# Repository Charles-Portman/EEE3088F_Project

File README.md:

# EEE3088F_Project
 
The project will be a Self-Contained Light Sensing Module.
This will include an ambient light digital sensor and an analog voltage divider using photoresistors (Amount dependant on budget).
The module will include EEEPROM and battery power.
The prupose of the Git is for the programming of the microcontroller to FTDI-USB converter, EEPROM read and write, Reading from the sensors using I2C and the on-board ADC of the microcintroller.

NOTE - Additionally a low power standby mode may be added

Proposed branches 
- Sensors
 - ADC sensing
 - Digital Sensing
- Storage
- External Communication

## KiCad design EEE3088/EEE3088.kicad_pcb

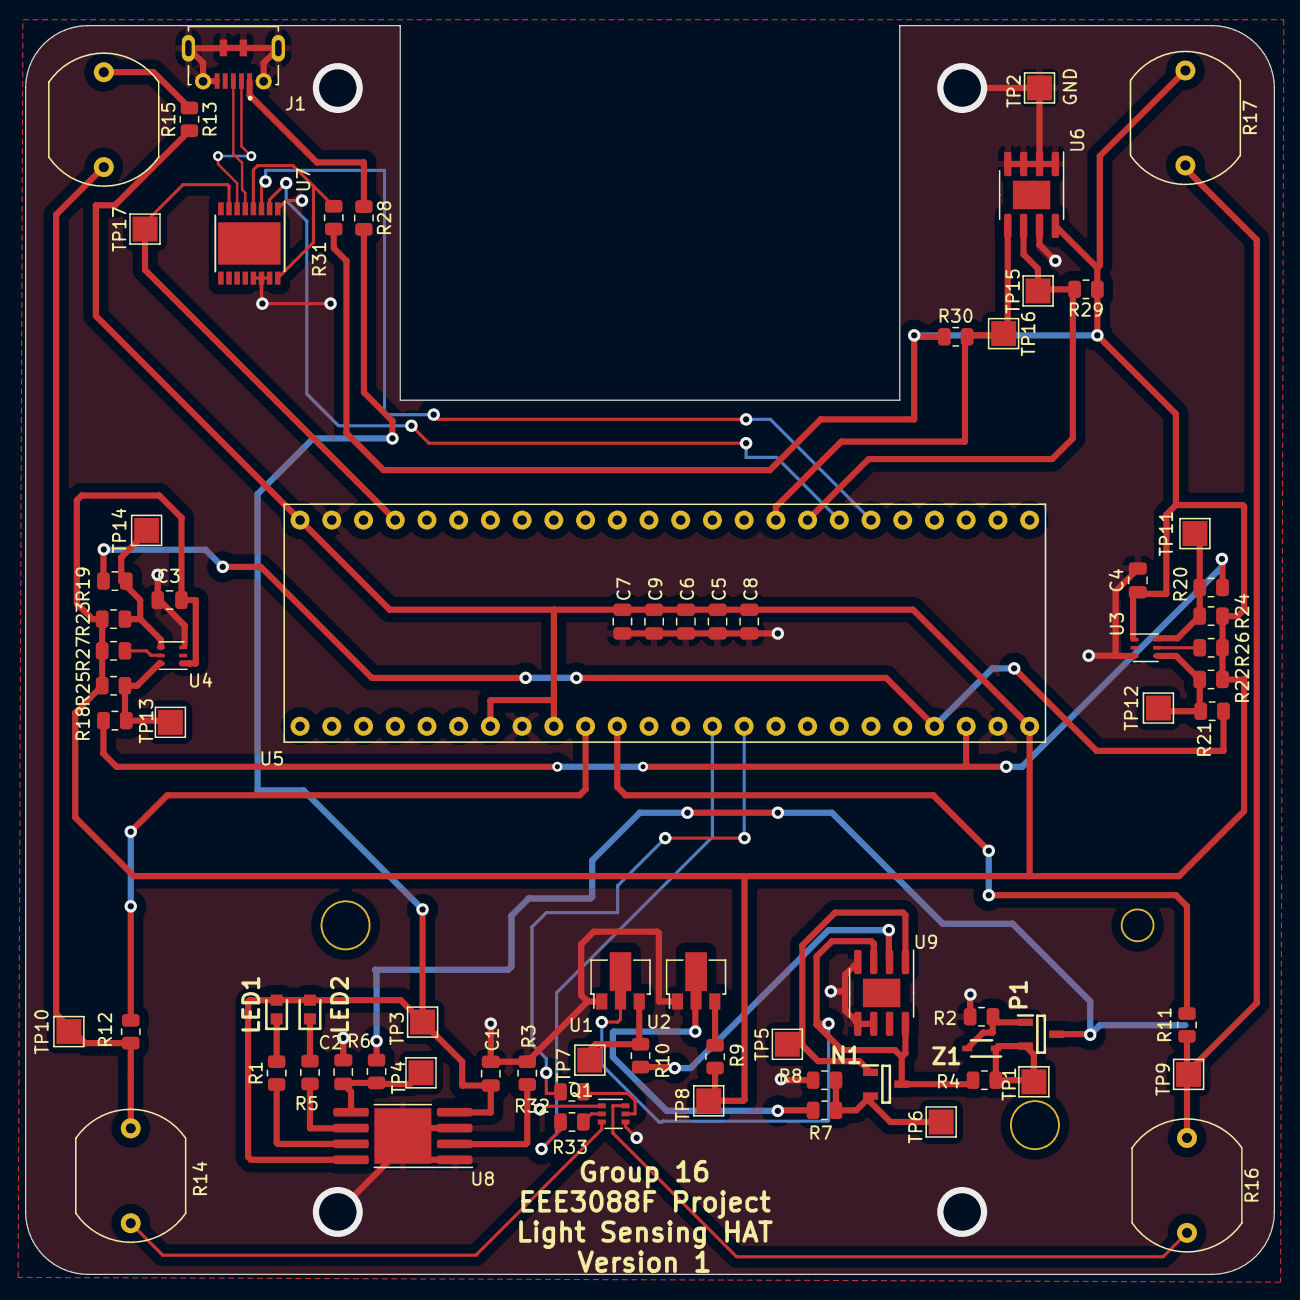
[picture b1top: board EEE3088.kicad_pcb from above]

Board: 2 copper layers, 100.0 x 100.0 mm, 76 parts (1 on the bottom side), 47 nets.

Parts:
Battery-Holder1: BH-18650-PC; 18650_Holder_SMD
C1, C2: 10uF; C_0805_2012Metric
C3, C4, C9: 1uF; C_0805_2012Metric
C5, C6: 100nF; C_0805_2012Metric
C7: 4.7uF; C_0805_2012Metric
C8: 10nF; C_0805_2012Metric
J1: MICROXNJ; SHOUHAN_MICROXNJ
LED1: Red; LEDC1608X70N
LED2: Green; LEDC1608X50N
N1: AO3400A; SOT95P280X125-3N
P1: AO3401A; SOT95P280X125-3N
Q1: MMDT2222A; SOT-363_SC-70-6
R1, R5: 1k; R_0805_2012Metric
R2: 100k; R_0805_2012Metric
R3: 1.2k; R_0805_2012Metric
R4, R6, R7, R9, R10, R11, R12, R13, R18, R19, R20, R21, R28, R31: 0; R_0805_2012Metric
R8: 1M; R_0805_2012Metric
R14, R15, R16, R17: LDR03; R_LDR_10x8.5mm_P7.6mm_Vertical
R22, R23, R24, R25, R26, R27: 10K; R_0805_2012Metric
R29, R30: 1.8k; R_0805_2012Metric
R32, R33: 1K; R_0805_2012Metric
TP1, TP2, TP3, TP4, TP5, TP6, TP7, TP8, TP9, TP10, TP11, TP12, TP13, TP14, TP15, TP16, TP17: TestPoint; TestPoint_Pad_2.0x2.0mm
U1, U2: HT7533-1; SOT-89-3
U3, U4: LTR-303ALS-01; Lite-On_LTR-303ALS-01
U5: Header; STM32F051C6T6
U6: AT24C256C-SSHL-T; SOIC-8-1EP_3.9x4.9mm_P1.27mm_EP2.29x3mm
U7: CH340G; HTSSOP-16-1EP_4.4x5mm_P0.65mm_EP3.4x5mm
U8: TP4056; SOP-8-1EP_4.57x4.57mm_P1.27mm_EP4.57x4.45mm
U9: MCP6002T-I_SN; SOIC-8-1EP_3.9x4.9mm_P1.27mm_EP2.29x3mm
Z1: MM3Z5V6C; SODFL2513X100N

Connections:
+3.3V: C3.1, C4.1, C5.1, C6.1, C7.1, C8.1, C9.1, R9.2, R13.2, R17.1, R22.1, R23.1, R24.1, R25.1, R26.1, R27.1, R29.1, R30.1, R31.1, TP8.1, U3.1 (VDD), U4.1 (VDD), U5.7 (NRST), U5.9 (V+), U5.24 (V+), U5.48 (V+), U6.8 (VCC)
+5V: C1.1, LED1.2, LED2.2, R28.2, TP3.1, U8.4 (VCC), U8.8 (CE)
/Microcontroller/Analogue_Enable1: R33.1, U5.14 (PA4)
/Microcontroller/Analogue_Enable2: R32.1, U5.15 (PA5)
/Microcontroller/EEPROM_SCL: R29.2, TP15.1, U5.32 (PA11), U6.6 (SCL)
/Microcontroller/EEPROM_SDA: R30.2, TP16.1, U5.33 (PA12), U6.5 (SDA)
/Microcontroller/LDR_Vout1: R11.2, U5.11 (PA1)
/Microcontroller/LDR_Vout2: R12.1, U5.10 (PA0)
/Microcontroller/SCLSense: R19.1, R21.1, U5.21 (PB10)
/Microcontroller/SDASense_1: R18.1, R20.2, U5.22 (PB11)
/Microcontroller/USB_D+: J1.3 (D+), U7.5 (UD+)
/Microcontroller/USB_D-: J1.2 (D-), U7.6 (UD-)
/Microcontroller/USB_RXD: U5.30 (PA9), U7.3 (RXD)
/Microcontroller/USB_TIMIN: TP17.1, U5.45 (PB8), U7.7 (XI)
/Microcontroller/USB_TXD: U5.31 (PA10), U7.2 (TXD)
/Power_Subsystem/3.3-back: R10.2, U9.2 (VINA-)
/Power_Subsystem/V-Reg: R7.2, U2.2 (VI)
/Power_Subsystem/V-pos: N1.3, R4.2, U1.2 (VI), U9.3 (VINA+), U9.8 (VDD)
/Power_Subsystem/Vbat: Battery-Holder1.1, P1.3, R6.2
GND: Battery-Holder1.2, C1.2, C2.2, C3.2, C4.2, C5.2, C6.2, C7.2, C8.2, C9.2, J1.5 (GND), J1.S1 (SHIELD), J1.S2 (SHIELD), J1.S3 (SHIELD), J1.S4 (SHIELD), J1.S5 (SHIELD), J1.S6 (SHIELD), Q1.1 (E1), Q1.4 (E2), R2.1, R3.1, R8.2, TP2.1, U1.1, U2.1, U3.3 (GND), U4.3 (GND), U5.8 (GND), U5.23 (GND), U5.47 (GND), U6.1 (A0), U6.2 (A1), U6.3 (A2), U6.4 (GND), U6.7 (WP), U7.1 (GND), U7.13 (~DTR), U7.14 (~RTS), U7.15 (RS232), U8.1 (TEMP), U8.3 (GND), U8.9 (EP), U9.4 (VSS), U9.5 (VINB+), U9.6 (VINB-)
unnamed: J1.1 (VBUS), R28.1
unnamed: LED1.1, R1.2
unnamed: LED2.1, R5.1
unnamed: N1.2, R7.1, R8.1, TP6.1
unnamed: Q1.2 (B1), R33.2
unnamed: Q1.6 (C1), R16.2
unnamed: Q1.5 (B2), R32.2
unnamed: Q1.3 (C2), R14.2
unnamed: R11.1, R16.1, R17.2, TP9.1
unnamed: R12.2, R14.1, R15.2, TP10.1
unnamed: R13.1, R15.1
unnamed: R10.1, TP7.1, U1.3 (VO)
unnamed: R9.1, U2.3 (VO)
unnamed: R26.2, U3.5 (INT)
unnamed: R21.2, R22.2, TP12.1, U3.4 (SCL)
unnamed: R20.1, R24.2, TP11.1, U3.6 (SDA)
unnamed: R27.2, U4.5 (INT)
unnamed: R19.2, R23.2, TP14.1, U4.4 (SCL)
unnamed: R18.2, R25.2, TP13.1, U4.6 (SDA)
unnamed: R31.2, U7.4 (V3), U7.16 (VCC)
unnamed: C2.1, R6.1, TP4.1, U8.5 (BAT)
unnamed: R3.2, U8.2 (PROG)
unnamed: R1.1, U8.7 (~CHRG)
unnamed: R5.2, U8.6 (~STDBY)
unnamed: N1.1, TP5.1, U9.1 (VOUTA)
unnamed: P1.1, R2.2, Z1.2 (A)
unnamed: P1.2, R4.1, TP1.1, Z1.1 (K)

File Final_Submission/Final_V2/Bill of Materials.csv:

Comment,Designator,Footprint,JLCPCB Part#
10uF Cap 0805,"C1, C2",0805_C,C15850
1uF Cap 0805,"C3, C4, C9",0805_C,C28323
100nF Cap 0805,"C5, C6",0805_C,C49678
4.7uF Cap 0805,C7,0805_C,C1779
10nF Cap 0805,C8,0805_C,C1710
USB Connector,J1,MICROXNJ,C404969
Red LED,LED1,LEDC1608X70N,C2286
Green LED,LED2,LEDC1608X50N,C72043
30V N-Channel MOSFET,N1,SOT95P280X125-3N,C20917
30V P-Channel MOSFET,P1,SOT95P280X125-3N,C15127
Dual NPN Transistor,Q1,SOT-363_SC-70-6,C96379
1k Resistor 0805,"R1, R5, R32, R33",0805_R,C17513
100k Resistor 0805,R2,0805_R,C149504
1.2k Resistor 0805,R3,0805_R,C17379
0 Resistor 0805,"R4, R6, R7, R9-R13, R18-R21, R28, R31",0805_R,C17477
1M Resistor 0805,R8,0805_R,C17514
LDR,R14-R17,R_LDR_10x8.5mm_P7.6mm_Vertical,C11287
10K Resistor 0805,R22-R27,0805_R,C17414
1.8k Res 0805,"R29, R30",0805_R,C17398
Voltage Regulator,"U1, U2",SOT-89-3,C14289
ALS,"U3, U4",LTR-303ALS-01,C364577
EEPROM,U6,SOIC-8-1EP_3.9x4.9mm_P1.27mm_EP2.29x3mm,C6482
USB Comms ,U7,HTSSOP-16-1EP_4.4x5mm_P0.65mm_EP3.4x5mm,C14267
Battery Charger,U8,SOP-8-1EP_4.57x4.57mm_P1.27mm_EP4.57x4.45mm,C16581
Op-Amp,U9,SOIC-8-1EP_3.9x4.9mm_P1.27mm_EP2.29x3mm,C7377
Zener diode,Z1,SODFL2513X100N,C48886

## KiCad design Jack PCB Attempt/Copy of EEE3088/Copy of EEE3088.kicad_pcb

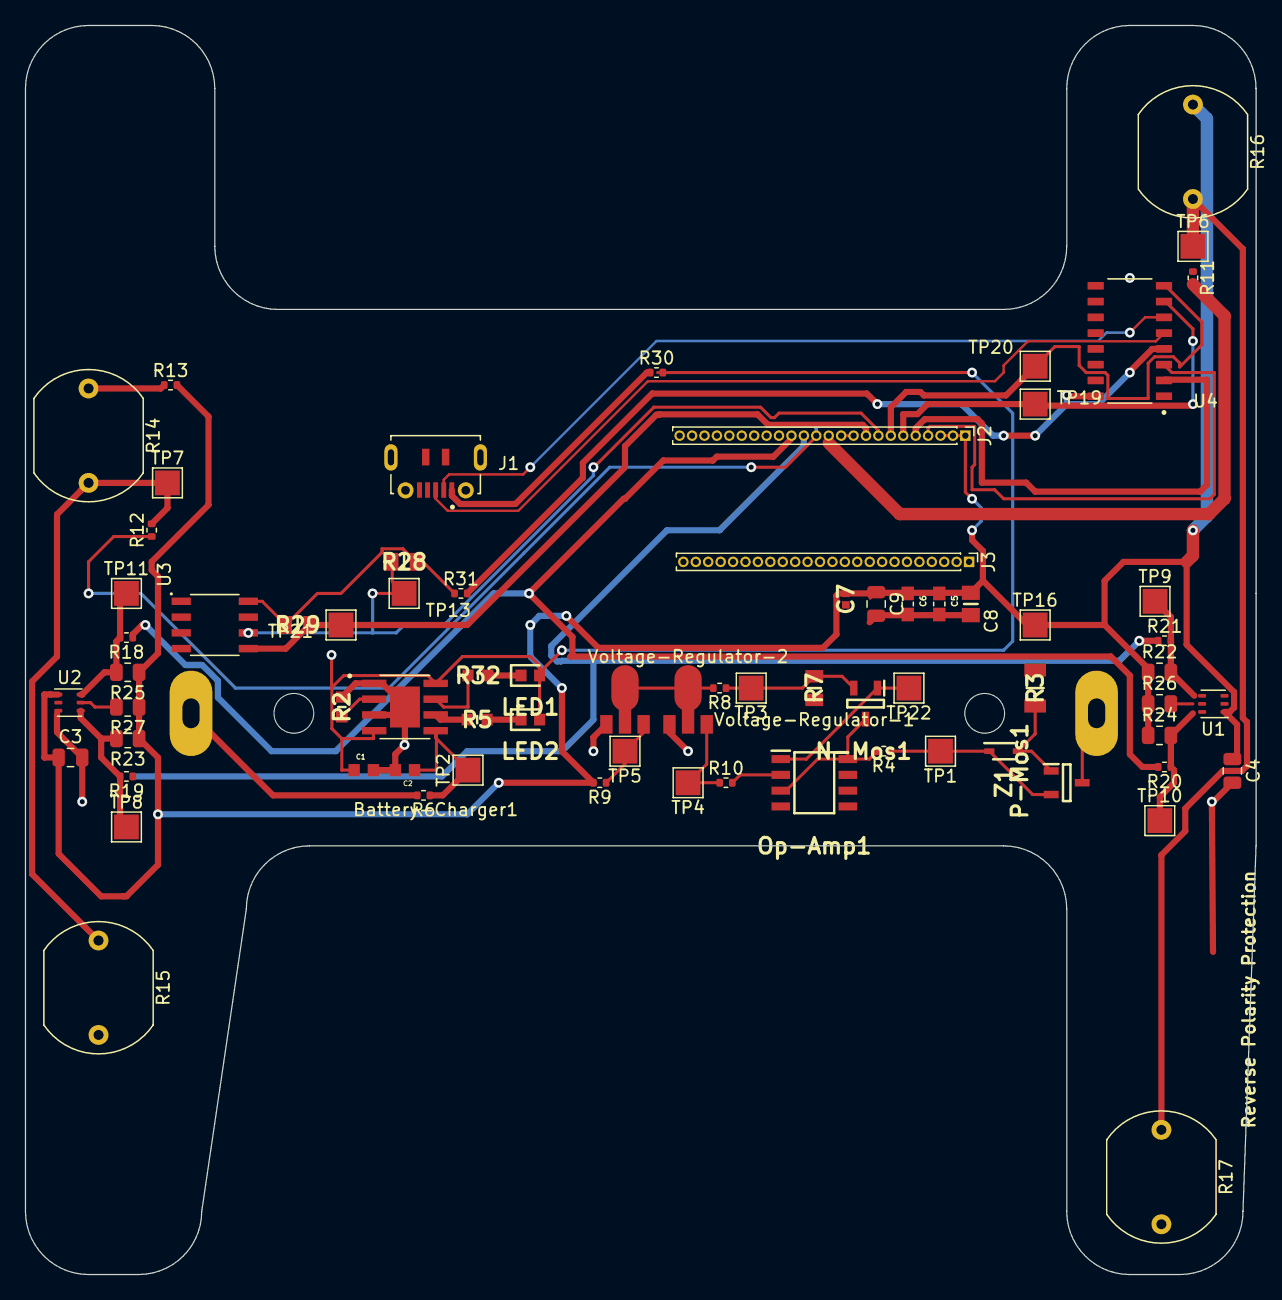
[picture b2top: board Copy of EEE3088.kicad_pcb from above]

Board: 2 copper layers, 99.1 x 100.5 mm, 74 parts (1 on the bottom side), 44 nets.

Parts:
Battery-Charger1: TP4056; SOP127P600X175-9N
Battery-Holder1: BH-18650-PC; BAT_BH-18650-PC
C1, C2: 10uF; CAPC1608X90N
C3, C4, C9: 1uF; C_0805_2012Metric
C5, C6: 100nF; CAPC1608X90
C7: 4.7uF; CAPC1005X55N
C8: 10nF; CAPC2012X140N
J1: MICROXNJ; SHOUHAN_MICROXNJ
J2, J3: Conn_01x24; PinHeader_1x24_P1.00mm_Vertical
LED1: Red; LEDC1608X70N
LED2: Green; LEDC1608X50N
N-Mos1: AO3400A; SOT95P280X125-3N
Op-Amp1: MCP6002T-I_SN; SOIC127P600X175-8N
P-Mos1: AO3401A; SOT95P280X125-3N
R2: 1.2k; RESC1608X55N
R3: 100k; RESC3116X65N
R4, R6, R8, R9, R10, R11, R12, R13, R18, R19, R20, R21, R30, R31: 0; R_0402_1005Metric
R5, R32: 1k; RESC1608X55N
R7: 1M; RESC2013X65N
R14, R15, R16, R17: LDR03; R_LDR_10x8.5mm_P7.6mm_Vertical
R22, R23, R24, R25, R26, R27: 10K; R_0805_2012Metric
R28, R29: 1.8k; RESC2013X65N
TP1, TP2, TP3, TP4, TP5, TP6, TP7, TP8, TP9, TP10, TP11, TP13, TP16, TP19, TP20, TP21, TP22: TestPoint; TestPoint_Pad_2.0x2.0mm
U1, U2: LTR-303ALS-01; Lite-On_LTR-303ALS-01
U3: AT24C256C-SSHL-T; SOIC127P600X175-8N
U4: CH340G; SOIC127P600X180-16N
Voltage-Regulator-1, Voltage-Regulator-2: HT7533-1; SOT89
Z1: MM3Z5V6C; SODFL2513X100N

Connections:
+3.3V: C3.1, C4.1, C5.1, C6.1, C7.1, C8.1, C9.1, J2.1, J2.2, J2.3, R9.2, R13.2, R16.1, R22.1, R23.1, R24.1, R25.1, R26.1, R27.1, TP16.1, U1.1 (VDD), U2.1 (VDD)
+3V3: R28.1, R29.1, R31.1, U3.8 (VCC)
+5V: Battery-Charger1.4 (VCC), Battery-Charger1.8 (CE), C1.1, LED1.2, LED2.2, R30.2
/Microcontroller/EEPROM_SCL: J2.8, R28.2, TP13.1, U3.6 (SCL)
/Microcontroller/EEPROM_SDA: J2.9, R29.2, TP21.1, U3.5 (SDA)
/Microcontroller/LDR_Vout1: J2.12, R11.2
/Microcontroller/LDR_Vout2: J2.13, R12.1
/Microcontroller/SCLSense: J2.14, R19.1, R21.1
/Microcontroller/SDASense: J2.15, R18.1, R20.2
/Microcontroller/USB_D+: J1.3 (D+), U4.5 (UD+)
/Microcontroller/USB_D-: J1.2 (D-), U4.6 (UD-)
/Microcontroller/USB_RXD: J2.4, U4.3 (RXD)
/Microcontroller/USB_TIMIN: J2.6, TP19.1, U4.7 (XI)
/Microcontroller/USB_TIMOUT: J2.7, TP20.1, U4.8 (XO)
/Microcontroller/USB_TXD: J2.5, U4.2 (TXD)
/Power_Subsystem/3.3-back: Op-Amp1.2 (VINA-), R10.2
/Power_Subsystem/V-Reg: R8.2, Voltage-Regulator-1.2 (VI), Voltage-Regulator-1.2@1 (VI), Voltage-Regulator-2.2 (VI), Voltage-Regulator-2.2@1 (VI)
/Power_Subsystem/V-pos: N-Mos1.3, Op-Amp1.3 (VINA+), Op-Amp1.8 (VDD), R4.2
/Power_Subsystem/Vbat: Battery-Holder1.N, R6.2
GND: Battery-Charger1.1 (TEMP), Battery-Charger1.3 (GND), Battery-Charger1.9 (EP), C1.2, C2.2, C3.2, C4.2, C5.2, C6.2, C7.2, C8.2, C9.2, J1.5 (GND), J1.S1 (SHIELD), J1.S2 (SHIELD), J1.S3 (SHIELD), J1.S4 (SHIELD), J1.S5 (SHIELD), J1.S6 (SHIELD), J2.10, J2.11, Op-Amp1.4 (VSS), Op-Amp1.5 (VINB+), Op-Amp1.6 (VINB-), R2.1, R3.1, R7.2, R15.2, R17.2, U1.3 (GND), U2.3 (GND), U3.1 (A0), U3.2 (A1), U3.3 (A2), U3.4 (GND), U3.7 (WP), U4.1 (GND), U4.13 (~DTR), U4.14 (~RTS), U4.15 (RS232), Voltage-Regulator-1.1, Voltage-Regulator-2.1
unnamed: Battery-Charger1.5 (BAT), C2.1, R6.1, TP2.1
unnamed: Battery-Charger1.2 (PROG), R2.2
unnamed: Battery-Charger1.7 (~CHRG), R32.1
unnamed: Battery-Charger1.6 (~STDBY), R5.2
unnamed: Battery-Holder1.P, P-Mos1.3
unnamed: J1.1 (VBUS), R30.1
unnamed: LED1.1, R32.2
unnamed: LED2.1, R5.1
unnamed: N-Mos1.2, R7.1, R8.1, TP3.1
unnamed: N-Mos1.1, Op-Amp1.1 (VOUTA), TP22.1
unnamed: R11.1, R16.2, R17.1, TP6.1
unnamed: R12.2, R14.2, R15.1, TP7.1
unnamed: R13.1, R14.1
unnamed: R26.2, U1.5 (INT)
unnamed: R21.2, R22.2, TP9.1, U1.4 (SCL)
unnamed: R20.1, R24.2, TP10.1, U1.6 (SDA)
unnamed: R27.2, U2.5 (INT)
unnamed: R19.2, R23.2, TP8.1, U2.4 (SCL)
unnamed: R18.2, R25.2, TP11.1, U2.6 (SDA)
unnamed: R31.2, U4.4 (V3), U4.16 (VCC)
unnamed: R10.1, TP4.1, Voltage-Regulator-1.3 (VO)
unnamed: R9.1, TP5.1, Voltage-Regulator-2.3 (VO)
unnamed: P-Mos1.1, R3.2, Z1.2 (A)
unnamed: P-Mos1.2, R4.1, TP1.1, Z1.1 (K)

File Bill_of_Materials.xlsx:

Reference | Value | Footprint | Description | Extended | JLC Part Number | Manufacturer_Part_Number | Price | Qty | Price
C8 | 10nF | 10n Cap CL21B103KBANNNC:CAPC2012X140N | 10nF Cap 0805 | 0 | C1710 | CL21B103KBANNNC | 8.5000000000000006E-3 | 1 | 8.5000000000000006E-3
C7 | 4.7uF | 4.7n Cap LIB_0402B472K500NT:CAPC1005X55N | 4.7uF Cap 0805 | 0 | C1779 | CL21A475KAQNNNE | 1.12E-2 | 1 | 1.12E-2
LED1 | Red | MyRedLED:LEDC1608X70N | Red LED | 0 | C2286 | KT-0603R | 5.4000000000000003E-3 | 1 | 5.4000000000000003E-3
U3 | AT24C256C-SSHL-T | AT24C256C-SSHL-T EEPROM Chip:SOIC127P600X175-8N | EEPROM | 0 | C6482 | AT24C256C-SSHL-T | 0.46389999999999998 | 1 | 0.46389999999999998
Op-Amp1 | MCP6002T-I_SN | Myopamp:SOIC127P600X175-8N | Op-Amp | 0 | C7377 | MCP6002T-I/SN | 0.26600000000000001 | 1 | 0.26600000000000001
R14-R17 | LDR03 | OptoDevice:R_LDR_10x8.5mm_P7.6mm_Vertical | LDR | 1 | C11287 | GL3516 | 0.1298 | 4 | 3.5192000000000001
U4 | CH340G | CH340G Bridge:SOIC127P600X180-16N | USB Comms | 1 | C14267 | CH340G | 0.4733 | 1 | 3.4733000000000001
Voltage-Regulator-1, Voltage-Regulator-2 | HT7533-1 | HT7533-1:SOT89 | Voltage Regulator | 0 | C14289 | HT7533-1 | 0.12790000000000001 | 2 | 0.25580000000000003
P-Mos1 | AO3401A | MyPmos:SOT95P280X125-3N | 30V P-Channel MOSFET | 0 | C15127 | AO3401A | 7.6499999999999999E-2 | 1 | 7.6499999999999999E-2
C1, C2 | 10uF | CL10A106KP8NNNC:CAPC1608X90N | 10uF Cap 0805 | 0 | C15850 | CL21A106KAYNNNE | 1.3100000000000001E-2 | 2 | 2.6200000000000001E-2
Battery-Charger1 | TP4056 | TP4056:SOP127P600X175-9N | Battery Charger | 0 | C16581 | TP4056-42-ESOP8 | 0.21210000000000001 | 1 | 0.21210000000000001
2 | 1.2k | My1.2k:RESC1608X55N | 1.2k Resistor 0805 | 0 | C17379 | 0805W8F1201T5E | 1.8E-3 | 1 | 1.8E-3
R28, R29 | 1.8k | 1.8k Ohm Resistor:RESC2013X65N | 1.8k Res 0805 | 0 | C17398 | 0805W8F1801T5E | 1.6999999999999999E-3 | 2 | 3.3999999999999998E-3
R22-R27 | 10K | Resistor_SMD:R_0805_2012Metric | 10K Resistor 0805 | 0 | C17414 | 0805W8F1002T5E | 1E-3 | 6 | 6.0000000000000001E-3
R4, R6, R8-R13, R18-R21, R30, R31 | 0 | Resistor_SMD:R_0402_1005Metric | 0 Res 0805 | 0 | C17477 | 0805W8F0000T5E | 2.2000000000000001E-3 | 14 | 3.0800000000000001E-2
R5, R32 | 1k | RESC1608X55N | 1k Res 0805 | 0 | C17513 | 0805W8F1001T5E | 2.0999999999999999E-3 | 2 | 4.1999999999999997E-3
7 | 1M | My1M:RESC2013X65N | 1M Resistor 0805 | 0 | C17514 | 0805W8F1004T5E | 1.6000000000000001E-3 | 1 | 1.6000000000000001E-3
N-Mos1 | AO3400A | MyNmos:SOT95P280X125-3N | 30V N-Channel MOSFET | 0 | C20917 | AO3400A | 7.8700000000000006E-2 | 1 | 7.8700000000000006E-2
Z1 | MM3Z5V6C | MyZener:SODFL2513X100N | Zener diode | 1 | C48886 | MM3Z5V6 | 1.8200000000000001E-2 | 1 | 3.0182000000000002
C5, C6 | 100nF | 100n CC0603KRX7R9BB104:CAPC1608X90 | 100nF Cap 0805 | 0 | C49678 | CC0805KRX7R9BB104 | 4.5999999999999999E-3 | 2 | 9.1999999999999998E-3
LED2 | Green | MyGreenLED:LEDC1608X50N | Green LED | 0 | C72043 | 19-217/GHC-YR1S2/3T | 2.64E-2 | 1 | 2.64E-2
3 | 100k | My100k:RESC3116X65N | 100k Resistor 0805 | 0 | C149504 | 0805W8F1003T5E | 1.6999999999999999E-3 | 1 | 1.6999999999999999E-3
U1, U2 | LTR-303ALS-01 | OptoDevice:Lite-On_LTR-303ALS-01 | ALS | 1 | C364577 | LTR-303ALS-01 | 0.37619999999999998 | 2 | 3.7523999999999997
J1 | MICROXNJ | MICROXNJ:SHOUHAN_MICROXNJ | USB Connector | 1 | C404969 | MicroXNJ | 3.3300000000000003E-2 | 1 | 3.0333000000000001
C3, C4, C9 | 1uF | Capacitor_SMD:C_0805_2012Metric | 1uF Cap 0805 | 1 | C2976902 | CA45B-A-16V-1UF-k | 5.33E-2 | 3 | 3.1598999999999999
Battery-Holder1 | BH-18650-PC | BH-18650-PC:BAT_BH-18650-PC | Battery Holder | 0 | DNP | DNP | 0 | 1 | 0
J2, J3 | Conn_01x24 | Connector_PinHeader_1.00mm:PinHeader_1x24_P1.00mm_Vertical | STM Connector | 0 | DNP | DNP | 0 | 2 | 0
TP1-TP14, TP19-TP22 | TestPoint | TestPoint:TestPoint_Pad_2.0x2.0mm | Test Point | 0 | DNP | DNP | 0 | 18 | 0
 |  |  |  |  |  |  |  |  | 21.445699999999999 | 107.2285

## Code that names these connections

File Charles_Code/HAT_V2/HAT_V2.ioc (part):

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Mcu.Name=STM32F051C6Tx
Mcu.Package=LQFP48
Mcu.UserName=STM32F051C6Tx
PA0.Mode=IN0
PA0.Signal=ADC_IN0
PA1.Mode=IN1
PA1.Signal=ADC_IN1
PA10.Mode=Asynchronous
PA10.Signal=USART1_RX
PA4.GPIOParameters=PinState
PA4.PinState=GPIO_PIN_SET
PA4.Signal=GPIO_Output
PA5.GPIOParameters=PinState
PA5.PinState=GPIO_PIN_SET
PA5.Signal=GPIO_Output
PA9.Mode=Asynchronous
PA9.Signal=USART1_TX
board=custom

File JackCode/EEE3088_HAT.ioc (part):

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Mcu.Name=STM32F051R8Tx
Mcu.Package=LQFP64
Mcu.UserName=STM32F051R8Tx
PA10.Mode=Asynchronous
PA10.Signal=USART1_RX
PA9.Mode=Asynchronous
PA9.Signal=USART1_TX
PB10.Mode=I2C
PB10.Signal=I2C2_SCL
PB11.Mode=I2C
PB11.Signal=I2C2_SDA
RCC.SYSCLKFreq_VALUE=48000000
RCC.SYSCLKSource=RCC_SYSCLKSOURCE_PLLCLK
board=STM32F0DISCOVERY
boardIOC=true

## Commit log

2023-02-24 Create Anologue_Sensor
2023-02-24 Create Digital_Sensor
2023-02-24 Create Ext_Communication
2023-02-24 Create Storage
2023-03-03 KiCAD FIles
2023-03-03 First night - c
2023-03-05 05/03
2023-03-05 Microcontroller Comms
    Finished my subsection
2023-03-05 Design Proposal
    Added a word doc with my section done. Just add yours when you can
2023-03-05 Design proposal - Q3 draft
2023-03-05 added BOM sensing
2023-03-05 another
2023-03-06 Updated design proposal Q3
2023-03-06 Updated Sense_cost
2023-03-06 Power Updates
    Updated part values
    Made a Excel sheet for BOM
2023-03-06 Proposal update
    Power update
2023-03-06 Design proposal edit
    formatting
2023-03-11 Power update
    included Low voltage reg
2023-03-11 Rev_1_compl.
2023-03-12 Powe Update
2023-03-12 power updates
2023-03-12 New microcontroller section
    Finished and neatened up
2023-03-12 better microcontroller sheet
2023-03-12 Sense_V1_Submission
2023-03-12 power edit
2023-03-12 updated BOM
2023-03-14 BOM attempt
2023-03-14 BOM Update
2023-03-14 BOM_V1_Final
2023-03-16 Added test points & 0 Ohm
2023-03-16 Power - zener
2023-03-17 Start of PCB
2023-03-17 Lecture_PCB_Updates
2023-03-17 Light update to power
2023-03-17 power
2023-03-19 powere
2023-03-19 attempt to assign footprints
2023-03-19 adding footprints power
2023-03-19 Started Microcontroller PCB
2023-03-20 Finished uC PCB connections
    Your mom helped
2023-03-20 pcb_Sense_Initial
2023-03-20 no change
2023-03-20 uC parts added onto PCB properly
2023-03-20 Power PCB edit
2023-03-20 Power wires
2023-03-20 PCB_Update- DO NOT MOVE THE FREAKIN SENSORS
2023-03-20 power wiring
2023-03-20 power wriring
2023-03-21 uC PCB routing except power
2023-03-21 Power lines
2023-03-21 Sense_Wiring
2023-03-21 Gerbers added
2023-03-26 C-Branch
2023-03-27 Made a copy of the PCB
2023-03-27 Finished adding test copy for myself
2023-03-27 Revert "Finished adding test copy for myself"
    This reverts commit 9deb3b97d8caa0a97fc282a8a19962864a0c81f9.
2023-03-27 PCB H design attempt
2023-03-31 Schematic updates
2023-04-01 Schematic + PCB Update
2023-04-02 PCB continued again
2023-04-02 PCD- stm header added
2023-04-02 Silkscreen changes
2023-04-03 PCB - POwer and MCU added
2023-04-03 PCB-Final
2023-04-03 GND connections updated
2023-04-03 Added group number and names
2023-04-03 Fixed Text
2023-04-03 Gerbs
2023-04-03 Gerbers_Final
2023-04-14 Battery footprint changed
2023-04-14 Gebs V2 + Github cleanup
2023-04-25 unimportant
2023-05-17 Code!
2023-05-18 code update
2023-05-18 c-code v2
2023-05-19 code testing
2023-05-19 code new
